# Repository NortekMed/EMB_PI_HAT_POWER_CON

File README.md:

# PI-HAT Power Control

**Raspberry Pi HAT with Real-Time Clock and Power Management**

---

## 📋 Overview

This KiCad project provides a Raspberry Pi HAT featuring:
- **M41T0M6F** Serial Real-Time Clock with battery backup
- **32.768 kHz** crystal oscillator for precise timekeeping
- Power control and management circuitry
- Standard Raspberry Pi 40-pin GPIO header compatibility

**Company:** NortekMed  
**Version:** v300326 (2026-03-30)  
**Design Tool:** KiCad 10.0

---

## 📂 Project Structure

```
PI-HAT_POWER_CON/
├── DOCUMENTATION/
│   └── datasheet/           # Component datasheets (11 components)
├── FABRICATION/
│   ├── GERBER_v300326.zip   # Manufacturing files (Gerber + drill)
│   └── PI-HAT_POWER_CON_3D_v300326.png
├── GERBER/                  # Individual Gerber layer files
├── MECHANICAL/              # Mechanical drawings and models
├── SCHEMATICS/              # Additional schematic resources
├── PI-HAT_POWER_CON.kicad_pcb    # PCB layout file
├── PI-HAT_POWER_CON.kicad_sch    # Schematic file
├── PI-HAT_POWER_CON.kicad_pro    # KiCad project file
└── NortekLogo.png
```

---

## 🔧 Key Components

| Component | Part Number | Description |
|-----------|-------------|-------------|
| **RTC** | M41T0M6F | STMicroelectronics Serial RTC |
| **Oscillator** | CC4V-T1A | 32.768 kHz crystal oscillator |
| **Diode** | BAT54C-7-F | Schottky diode array |
| **Battery Holder** | Keystone 3000 | CR1220 coin cell holder |
| **Connector** | 282834-2 | Terminal block |

---

## 📁 Manufacturing Files

**Production-ready Gerber files:**
- `FABRICATION/GERBER_v300326.zip` - Complete manufacturing package
  - Gerber layers (top, bottom, silkscreen, solder mask)
  - Drill files (PTH and NPTH)
  - Job report

**Component Documentation:**
- All datasheets available in `DOCUMENTATION/datasheet/`
- Bill of Materials with Farnell part numbers in schematic

---

## 🛠️ Technical Specifications

- **Board Type:** 2-layer PCB
- **Dimensions:** Standard Raspberry Pi HAT form factor
- **Mounting:** Compatible with Raspberry Pi mounting holes
- **Interface:** I2C for RTC communication
- **Power:** Operates from Raspberry Pi 3.3V/5V supply
- **Battery Backup:** CR1220 coin cell for RTC during power-off

---

## 🔋 Maintenance

### RTC Battery Replacement

The Real-Time Clock (M41T0M6F) requires a **CR1220 or CR1225 coin cell battery** to maintain accurate timekeeping when the Raspberry Pi is powered off.

**Battery Specifications:**
- **Type:** CR1220 or CR1225 Lithium coin cell (3V)
- **Holder:** Keystone 3000
- **Typical Lifespan:** 5-10 years (depending on usage)
- **Standby Current:** ~0.9 µA

**Replacement Procedure:**
1. Power off the Raspberry Pi and disconnect all cables
2. Gently press and release the battery from the Keystone 3000 holder
3. Insert new CR1220 or CR1225 battery with positive (+) side facing up
4. Verify battery orientation matches the polarity markings on the PCB
5. Reconnect and power on - box should be start with modem to update/set date

**⚠️ Important Notes:**
- Always use fresh, high-quality CR1220 or CR1225 batteries
- Do not force the battery into the holder
- Dispose of used batteries according to local regulations
- Battery backup only maintains RTC time; it does not power other circuits

---

## 📜 License

© 2026 NortekMed. All rights reserved.

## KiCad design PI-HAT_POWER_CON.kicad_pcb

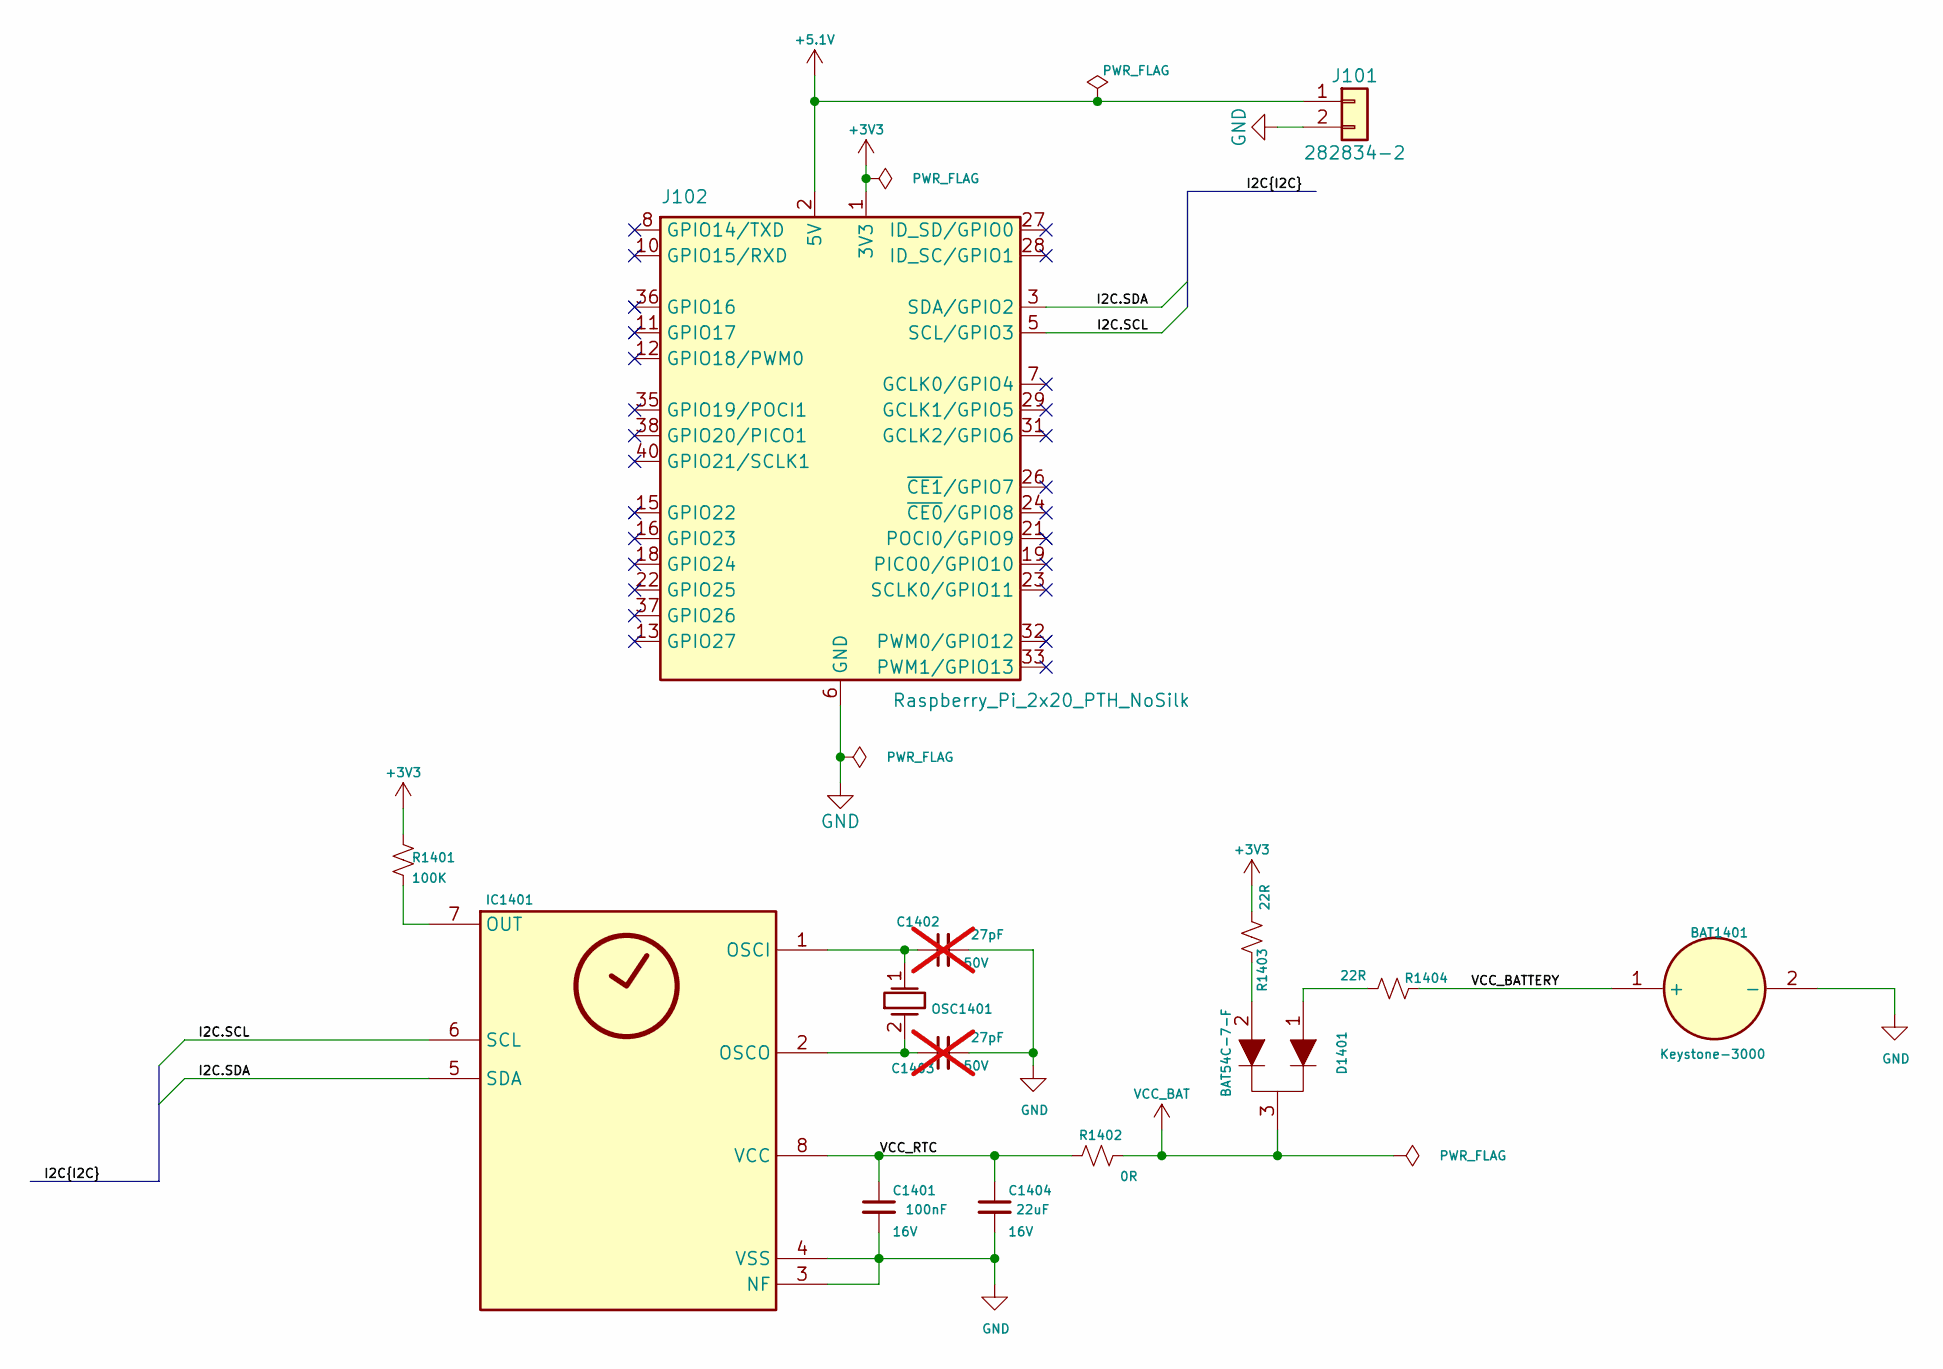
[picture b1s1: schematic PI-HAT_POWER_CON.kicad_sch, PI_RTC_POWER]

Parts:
BAT1401: Keystone-3000; T_Keystone_3000; mfr # 3000
C1401: 100nF; C_0603_1608Metric; TOLERANCE 10%; RATING 16V; mfr # VJ0603Y104KXJAT
C1402, C1403: 27pF; C_0603_1608Metric; TOLERANCE 5%; RATING 50V; mfr # *; not fitted
C1404: 22uF; C_1210_3225Metric; TOLERANCE 10%; RATING 16V; mfr # C1210C226K4PACTU
D1401: BAT54C-7-F; SOT-23-3; mfr # BAT54-7-F
IC1401: M41T0M6; SOIC-8_3.9x4.9mm_P1.27mm; mfr # M41T0M6
J101: 282834-2; TE_282834-2; mfr # 282834-2
J102: Raspberry_Pi_2x20_PTH_NoSilk; Raspberry_Pi_HAT_CON
OSC1401: CC4V-T1A; T_MC_CC4V-T1A; TOLERANCE 30ppm; mfr # CC4V-T1A
R1401: 100K; R_0603_1608Metric; RATING 63mW; TOLERANCE 5%; mfr # CRGS0603J100K
R1402: 0R; R_0603_1608Metric; RATING 100mW; TOLERANCE 1%; mfr # MCMR06X000 PTL
R1403, R1404: 22R; R_0603_1608Metric; RATING 100mW; TOLERANCE 5%; mfr # CRCW060322R0JNEA

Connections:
+3V3: J102.1 (3V3), J102.17 (3V3), R1401.1, R1403.2
+5.1V: J101.1, J102.2 (5V), J102.4 (5V)
/I2C.SCL: IC1401.6 (SCL), J102.5 (SCL/GPIO3)
/I2C.SDA: IC1401.5 (SDA), J102.3 (SDA/GPIO2)
/VCC_BATTERY: BAT1401.1 (+), R1404.1
/VCC_RTC: C1401.1, C1404.1, IC1401.8 (VCC), R1402.1
GND: BAT1401.2 (-), C1401.2, C1402.2, C1403.2, C1404.2, IC1401.3 (NF), IC1401.4 (VSS), J101.2, J102.6 (GND), J102.9 (GND), J102.14 (GND), J102.20 (GND), J102.25 (GND), J102.30 (GND), J102.34 (GND), J102.39 (GND)
unnamed: D1401.1, R1404.2
unnamed: D1401.2, R1403.1
unnamed: C1402.1, IC1401.1 (OSCI), OSC1401.1 (OSC1)
unnamed: C1403.1, IC1401.2 (OSCO), OSC1401.2 (OSC2)
unnamed: IC1401.7 (OUT), R1401.2
VCC_BAT: D1401.3, R1402.2

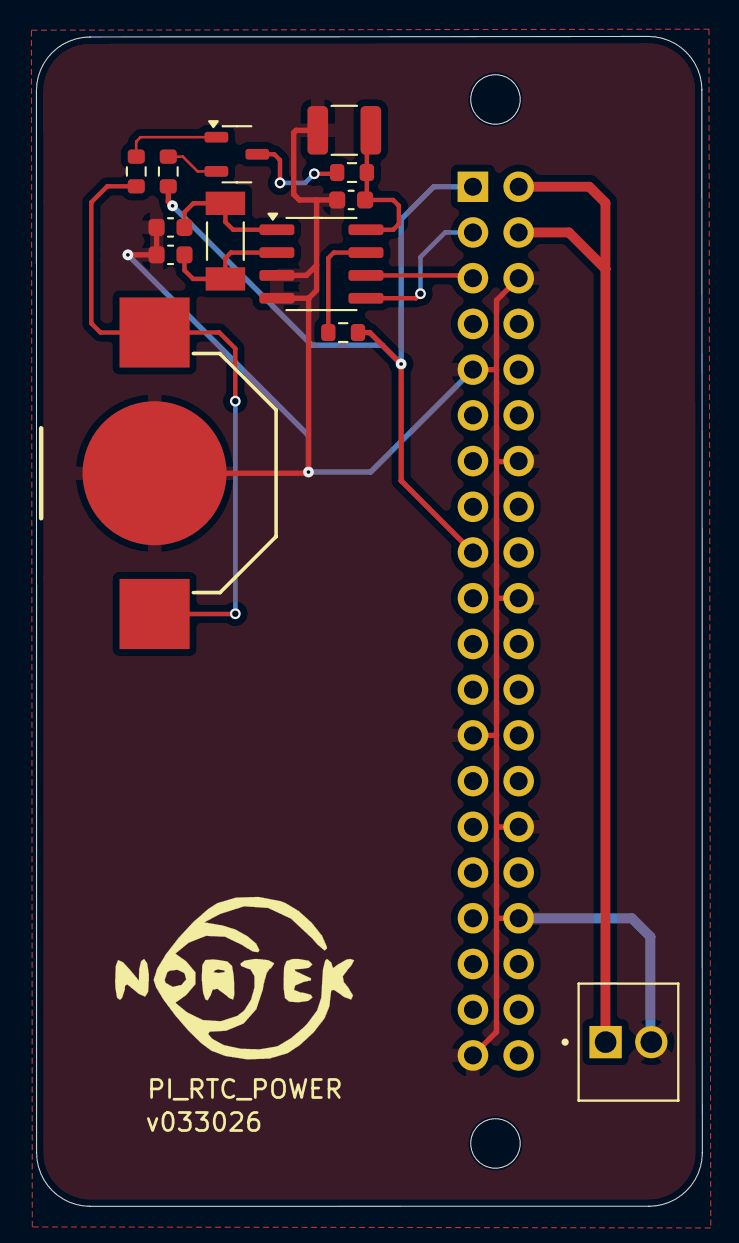
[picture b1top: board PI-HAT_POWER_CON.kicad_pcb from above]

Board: 2 copper layers, 37.0 x 65.0 mm, 14 parts (0 on the bottom side), 13 nets.

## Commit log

2026-03-27 Initial commit: add KiCad project and essential files, omitting generated and ignored files
2026-03-27 Add M41T0M6 RTC component to project schematic, PCB, and project settings
2026-03-28 Add persistent segmented project memory for chat summary and future recall
2026-03-28 Route PCB: Complete all nets, DRC clear, power and RTC connectivity verified
2026-03-30 Update README with project documentation and add 3D render v300326
    - Replace template README with comprehensive project documentation
    - Add maintenance section with RTC battery replacement procedure (CR1220/CR1225)
    - Include 3D isometric render of PCB (1176x872px, high quality)
    - Document key components, manufacturing files, and technical specifications
    - Reference GERBER_v300326.zip and component datasheets
    - Add project structure and NortekMed branding
2026-03-30 prepare for v300326 production
2026-04-02 remove ignoring FABRICATION
